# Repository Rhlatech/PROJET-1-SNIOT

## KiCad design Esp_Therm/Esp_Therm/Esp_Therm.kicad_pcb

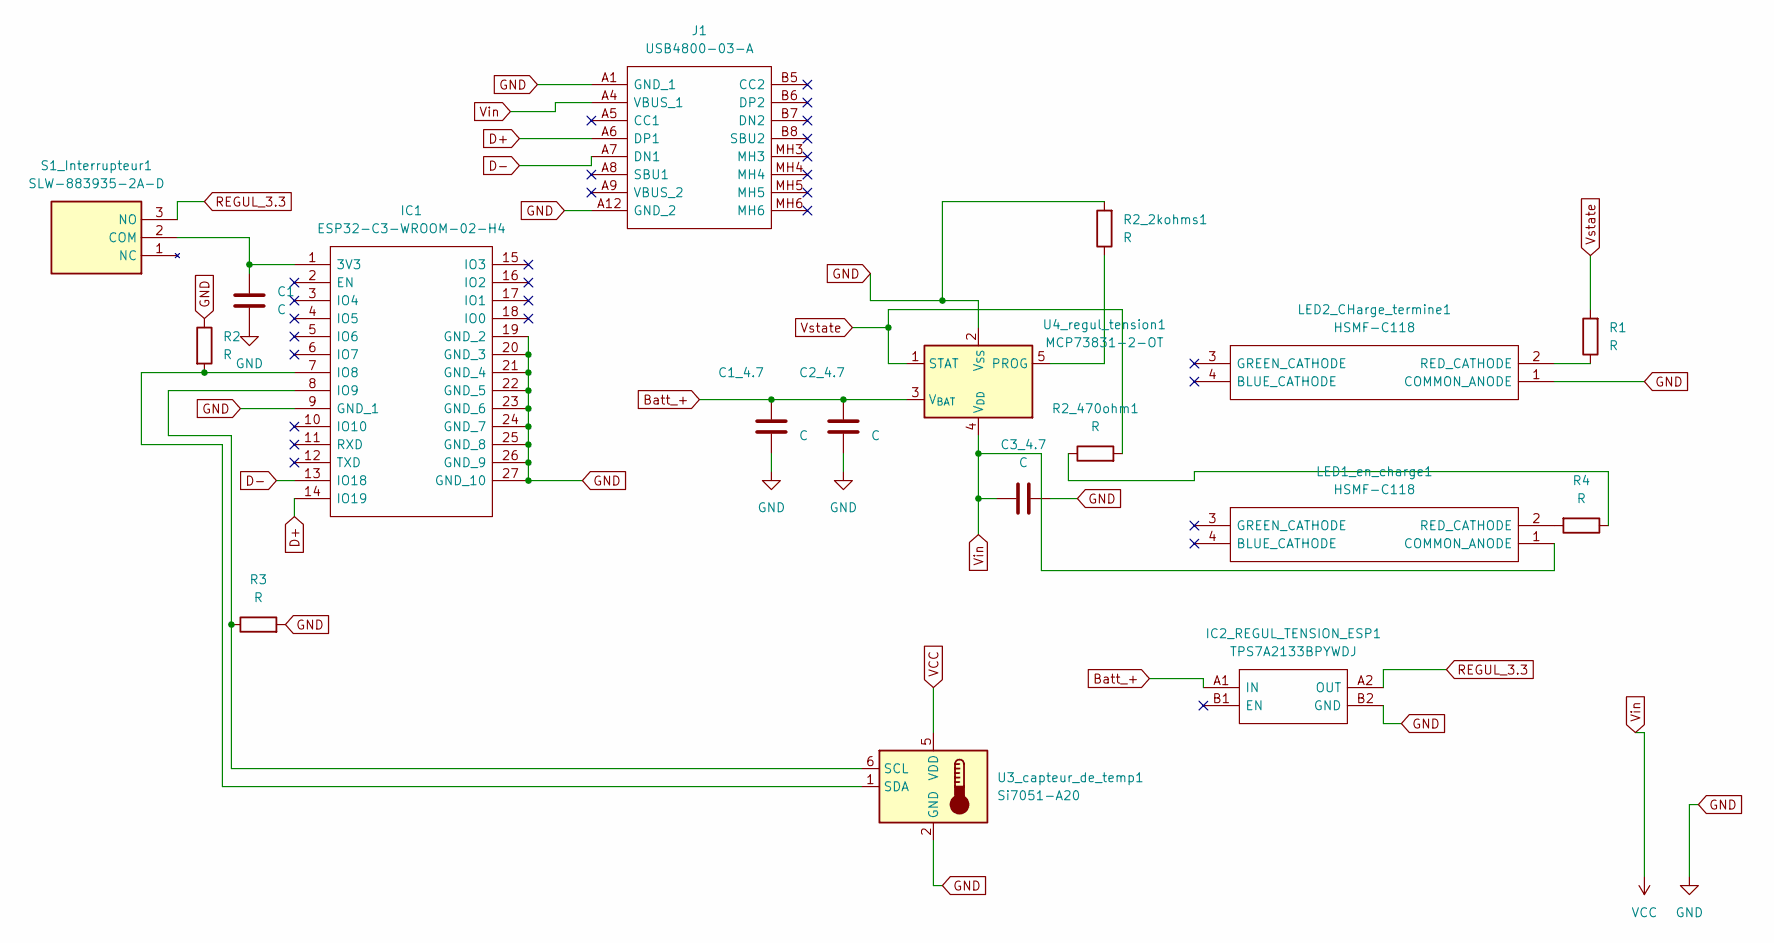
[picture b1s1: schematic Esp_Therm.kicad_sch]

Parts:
C1, C1_4.7, C2_4.7, C3_4.7: C; CP_EIA-1608-08_AVX-J
IC1: ESP32-C3-WROOM-02-H4; ESP32C3WROOM02H4; Mouser Part Number 356-ESP32C3WROOM02H4
IC2_REGUL_TENSION_ESP1: TPS7A2133BPYWDJ; Manufacturer_Part_Number TPS7A2133BPYWDJ; Mouser Part Number 595-TPS7A2133BPYWDJ
J1: USB4800-03-A; USB480003A; Mouser Part Number 640-USB4800-03-A
LED1_en_charge1, LED2_CHarge_termine1: HSMF-C118; HSMFC118; Manufacturer_Part_Number HSMF-C118; Mouser Part Number 630-HSMF-C118
R1, R2, R2_2kohms1, R2_470ohm1, R3, R4: R; R_0201_0603Metric
S1_Interrupteur1: SLW-883935-2A-D; SLW8839352AD; Mouser Part Number 179-SLW-883935-2A-D
U3_capteur_de_temp1: Si7051-A20; Capteur temp SI7051
U4_regul_tension1: MCP73831-2-OT; SOT-23-5

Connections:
Batt_+: C1_4.7.1, C2_4.7.1, IC2_REGUL_TENSION_ESP1.A1 (IN), U4_regul_tension1.3 (V_{BAT})
D+: IC1.14 (IO19), J1.A6 (DP1)
D-: IC1.13 (IO18), J1.A7 (DN1)
GND: C1.1, C1_4.7.2, C2_4.7.2, C3_4.7.1, IC1.9 (GND_1), IC1.19 (GND_2), IC1.20 (GND_3), IC1.21 (GND_4), IC1.22 (GND_5), IC1.23 (GND_6), IC1.24 (GND_7), IC1.25 (GND_8), IC1.26 (GND_9), IC1.27 (GND_10), IC2_REGUL_TENSION_ESP1.B2 (GND), J1.A1 (GND_1), J1.A12 (GND_2), LED2_CHarge_termine1.1 (COMMON_ANODE), R2.1, R2_2kohms1.2, R3.2, U3_capteur_de_temp1.2 (GND), U4_regul_tension1.2 (V_{SS})
unnamed: C1.2, IC1.1 (3V3), S1_Interrupteur1.2 (COM)
unnamed: IC1.7 (IO8), R2.2, U3_capteur_de_temp1.1 (SDA)
unnamed: IC1.8 (IO9), R3.1, U3_capteur_de_temp1.6 (SCL)
unnamed: LED1_en_charge1.2 (RED_CATHODE), R4.2
unnamed: LED2_CHarge_termine1.2 (RED_CATHODE), R1.1
unnamed: R2_470ohm1.1, R4.1
unnamed: R2_2kohms1.1, U4_regul_tension1.5 (PROG)
REGUL_3.3: IC2_REGUL_TENSION_ESP1.A2 (OUT), S1_Interrupteur1.3 (NO)
VCC: C3_4.7.2, J1.A4 (VBUS_1), LED1_en_charge1.1 (COMMON_ANODE), U3_capteur_de_temp1.5 (VDD), U4_regul_tension1.4 (V_{DD})
Vstate: R1.2, R2_470ohm1.2, U4_regul_tension1.1 (STAT)

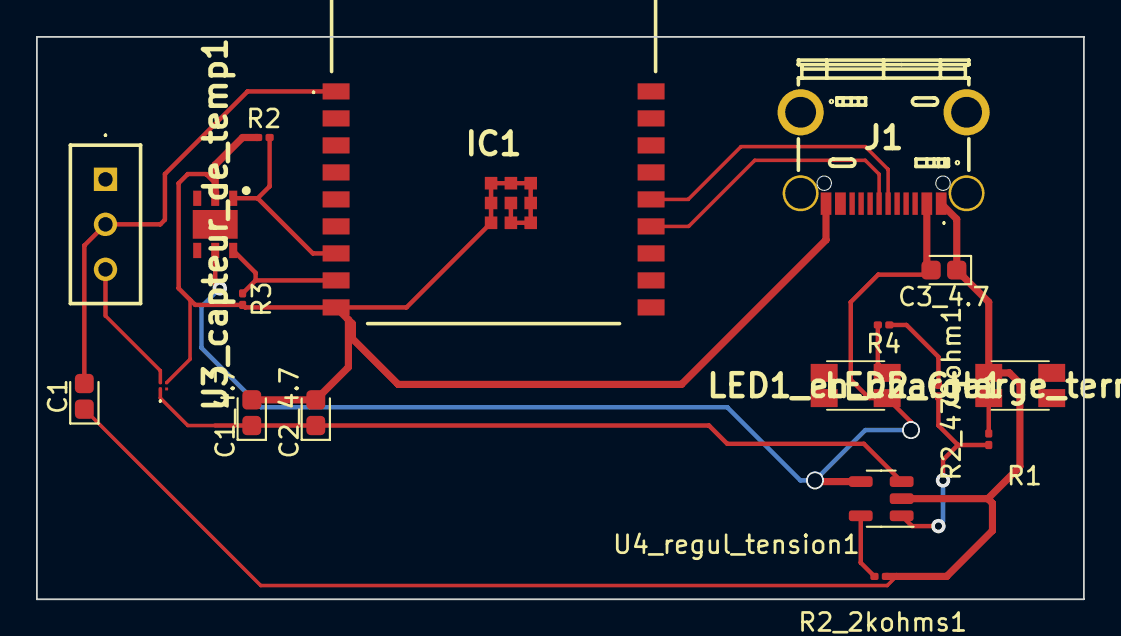
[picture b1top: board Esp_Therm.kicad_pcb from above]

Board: 2 copper layers, 58.2 x 31.2 mm, 18 parts (0 on the bottom side), 14 nets.

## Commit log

2023-10-25 Add files via upload
    The files about my project in IOT
2023-10-25 Add files via upload
    Nouvelle version
2023-11-02 Rapport à jour STEAM sensor + boutton + buzzer en cours
